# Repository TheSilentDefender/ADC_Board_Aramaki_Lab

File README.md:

# ADC Hub for pGRAMS
- Has 48 ADC channels and an optional voltage divider can be used for RTDs.
- The ADCs only support a range of 0-5V. Any input outside the range may damage the ADCs on board.
- The board outputs ADC integer values with a 12-bit resolution(0-4095)

## How to build
- Install platform.io on Visual Studio Code. You can also install it manually by following the documenation on [the website](https://platformio.org).
- Open the folder using VSC and wait for platform.io to initialize
- Open the platform.io side panel and click build. This should automatically build with the settings in the configuation file.

## How to flash
- Connect to the board in DFU mode or enter in "d" through serial (press the button on the top while you plug in the board)
- Assuming you followed the instuctions for building, you can click on build and upload which will automatic flash the board and restart it.
- If not you can download the bin file and flash it using dfu-util or any other DFU upgrade tool. For example, `sudo dfu-util -a 0 -i 0 -s 0x08000000:leave -D firmware.bin`.

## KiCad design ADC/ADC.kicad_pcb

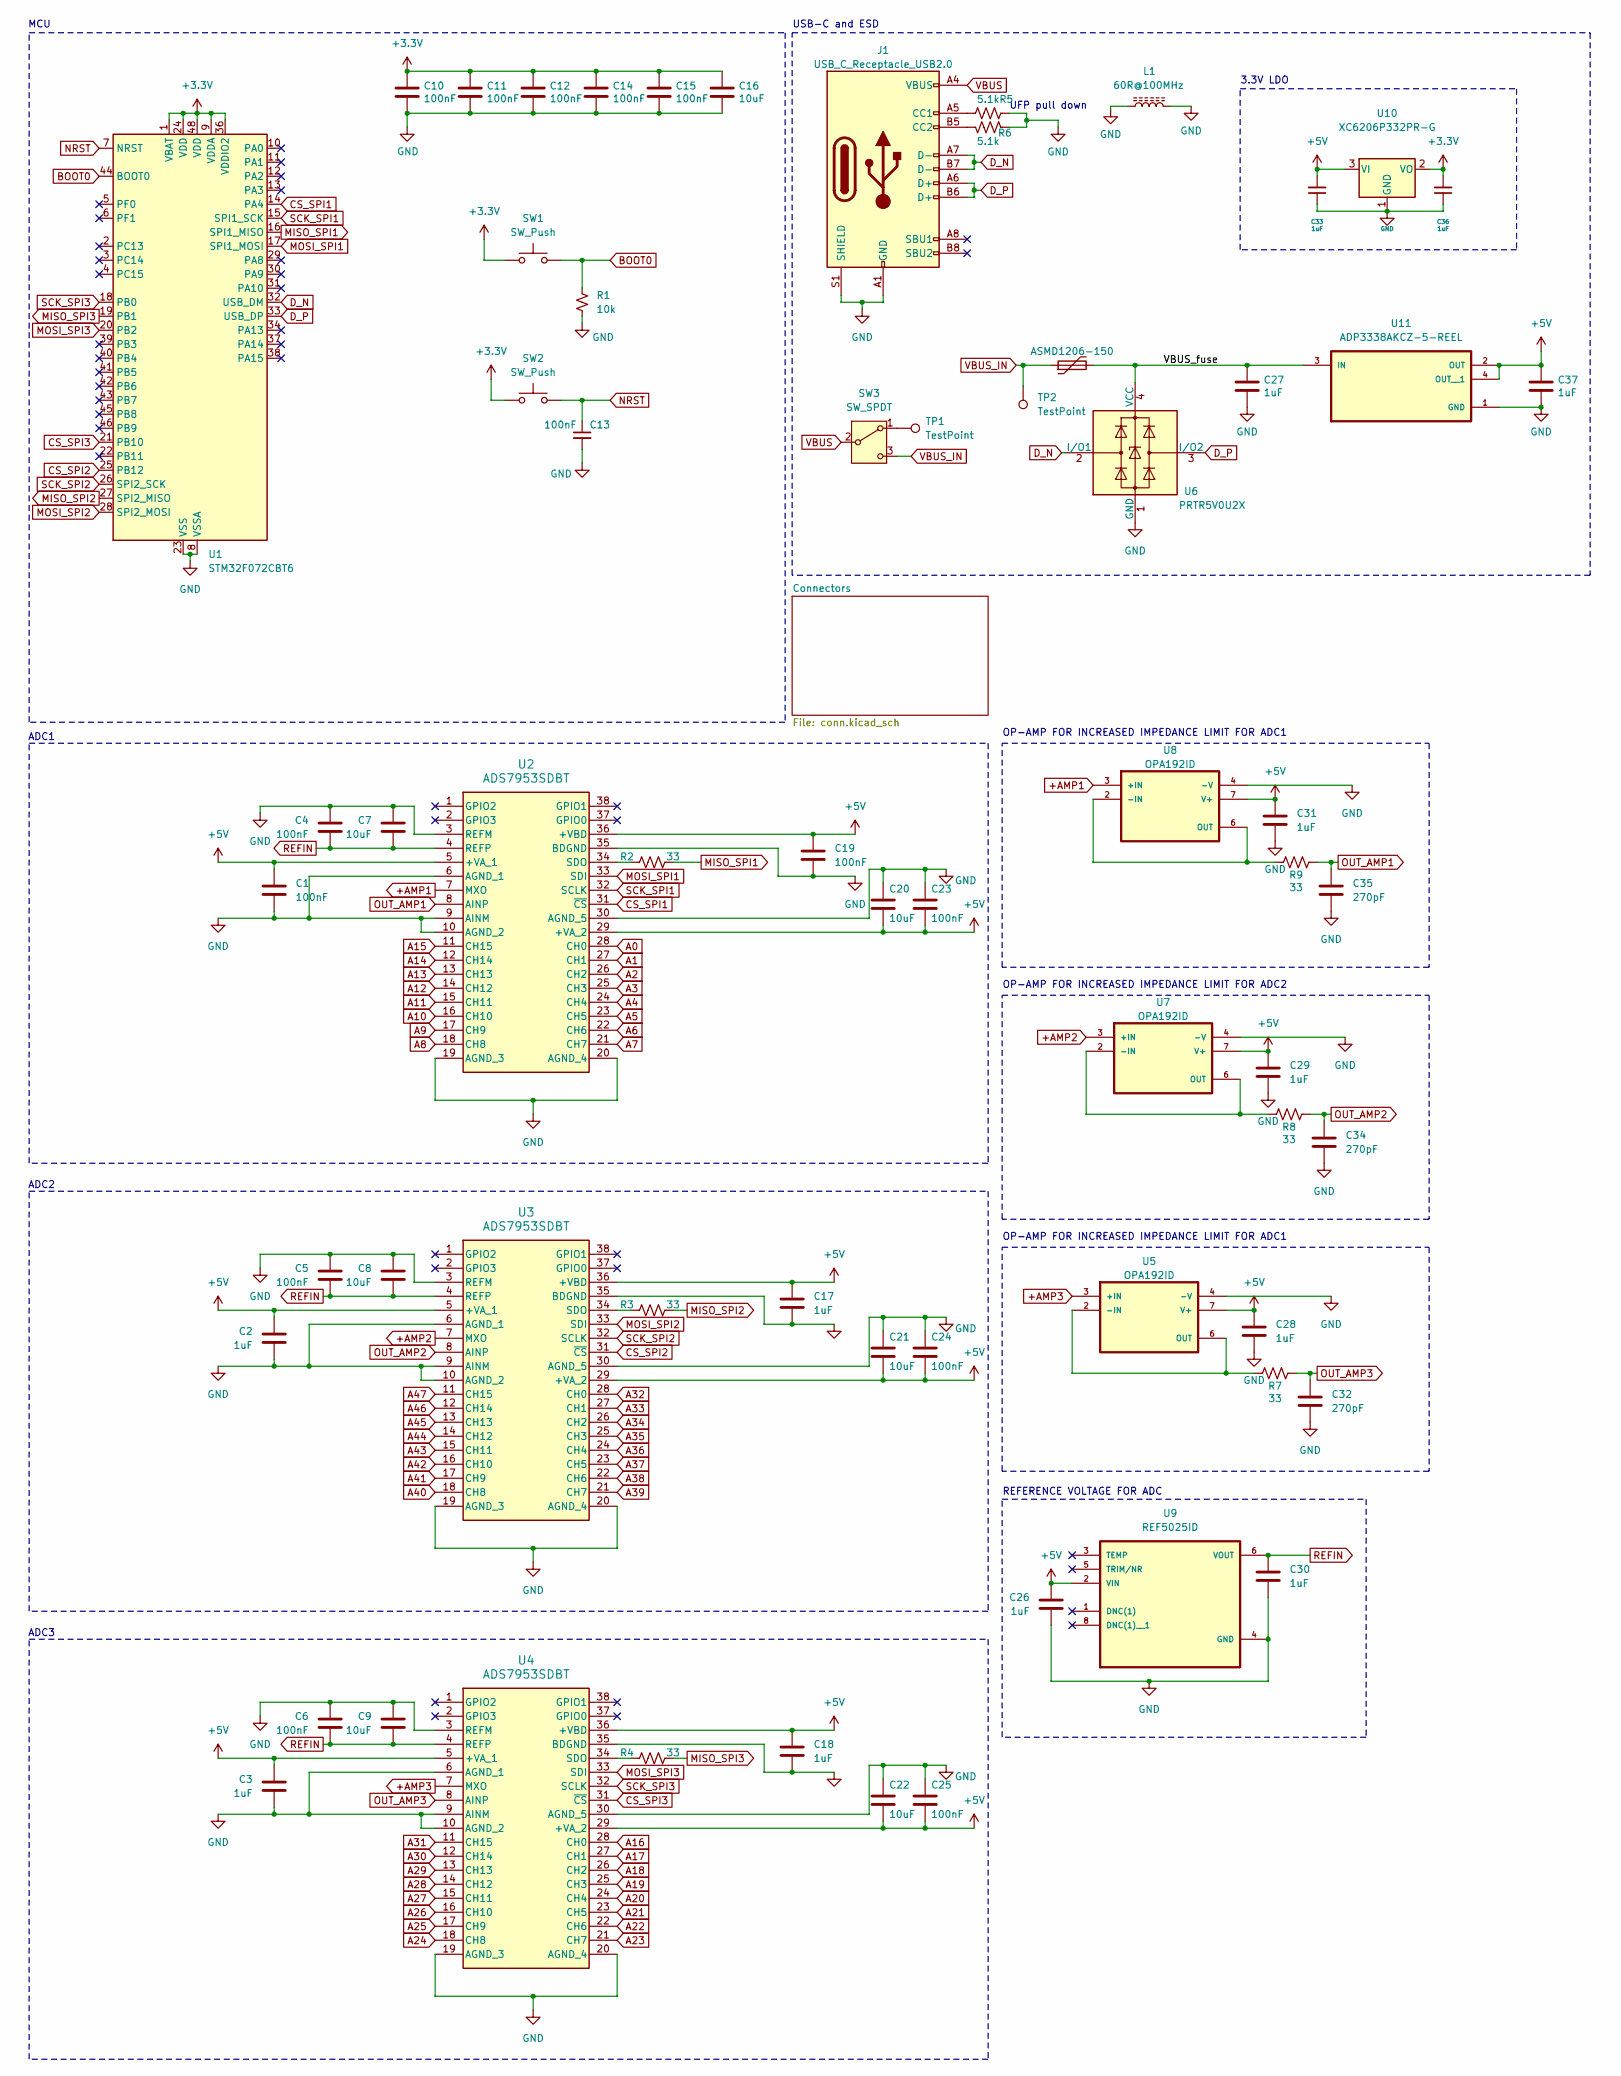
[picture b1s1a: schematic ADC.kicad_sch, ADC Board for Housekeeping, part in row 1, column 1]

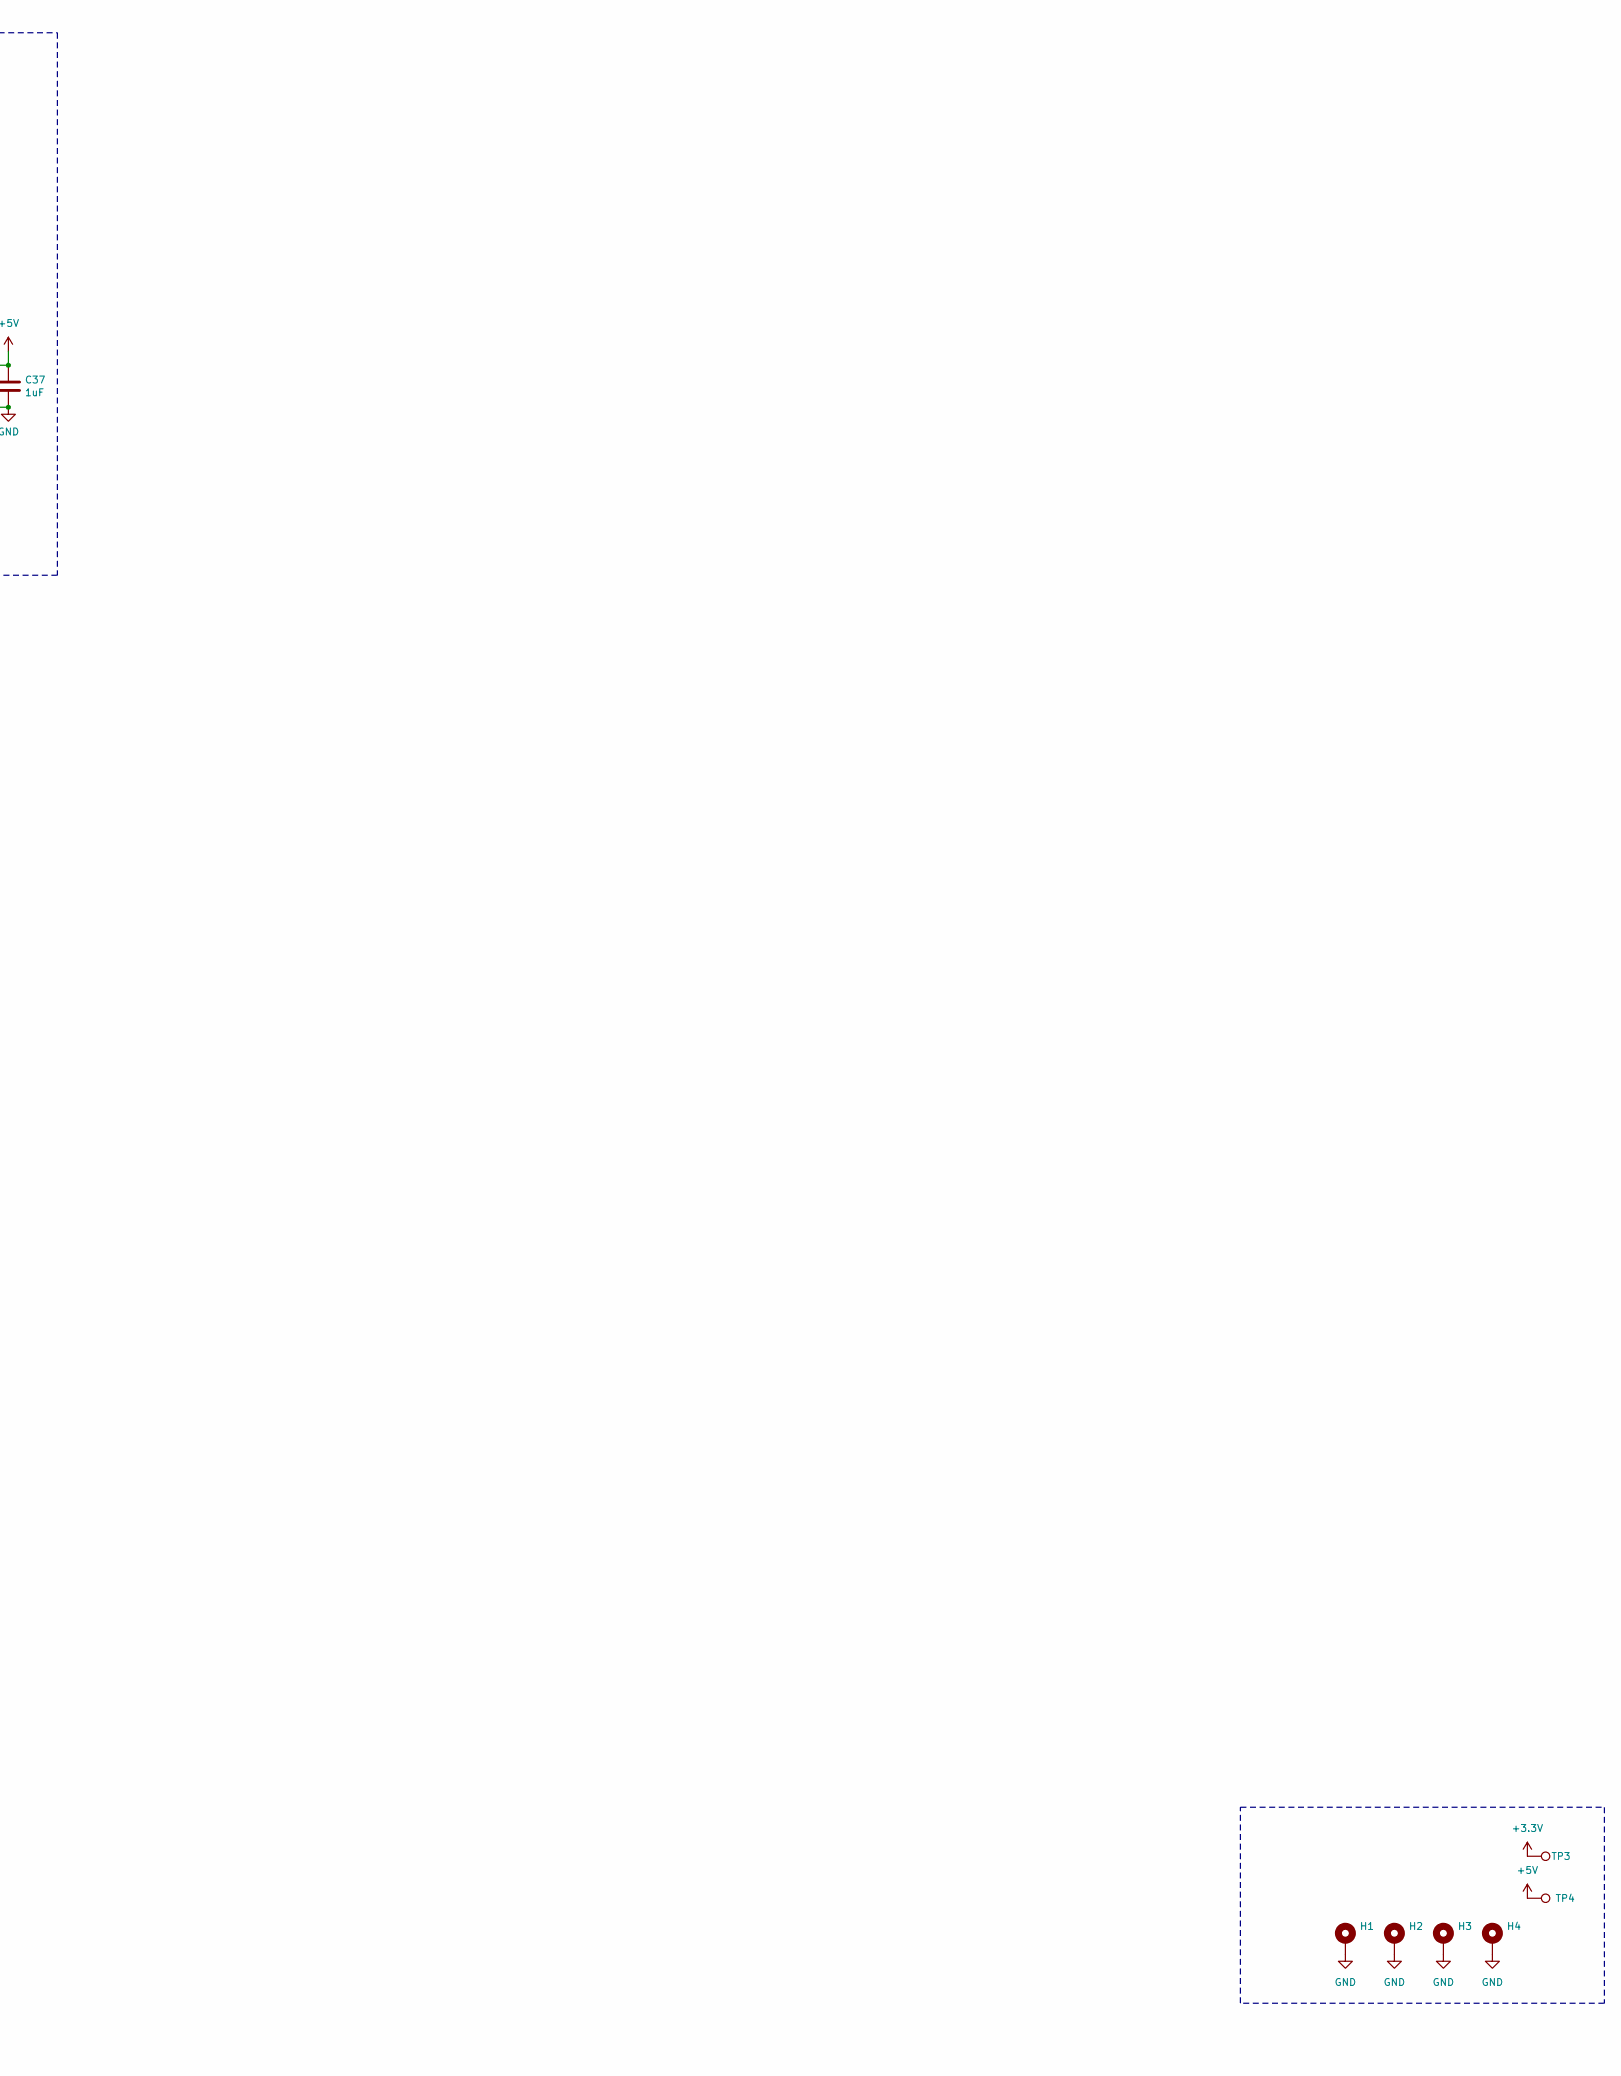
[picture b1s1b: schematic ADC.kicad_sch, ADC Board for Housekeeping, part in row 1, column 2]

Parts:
C1, C4, C5, C6, C19, C23, C24, C25: 100nF; C_0402_1005Metric
C2, C3, C17, C18, C26, C28, C29, C30, C31: 1uF; C_0402_1005Metric
C7, C8, C9, C16, C20, C21, C22: 10uF; C_0402_1005Metric
C10, C11, C12, C13, C14, C15: 100nF; C_0402_1005Metric; LCSC C307331
C27, C37: 1uF; C_0402_1005Metric; LCSC C307331
C32, C34, C35: 270pF; C_0402_1005Metric
C33, C36: 1uF; C_0402_1005Metric; LCSC C52923
F1: ASMD1206-150; Fuse_1206_3216Metric; LCSC C135341
H1, H2, H3, H4: MountingHole_Pad; MountingHole_3mm_Pad
J1: USB_C_Receptacle_USB2.0; USB_C_Receptacle_HRO_TYPE-C-31-M-12; JlcRotOffset 180
L1: 60R@100MHz; L_1206_3216Metric; Manufacturer Part No MLB3216-600P4A(f); LCSC C33600
R1: 10k; R_0402_1005Metric_Pad0.72x0.64mm_HandSolder
R2, R3, R4, R7, R8, R9: 33; R_0402_1005Metric_Pad0.72x0.64mm_HandSolder
R5, R6: 5.1k; R_0402_1005Metric_Pad0.72x0.64mm_HandSolder
SW1, SW2: SW_Push; SW_Push_SPST_NO_Alps_SKRK
SW3: SW_SPDT; SW_SPDT_CK_JS102011SAQN
TP1, TP2, TP3, TP4: TestPoint; TestPoint_Pad_D1.0mm
U1: STM32F072CBT6; LQFP-48_7x7mm_P0.5mm; JlcRotOffset 90
U2, U3, U4: ADS7953SDBT; DBT38
U5, U7, U8: OPA192ID; SOIC127P599X175-8N
U6: PRTR5V0U2X; SOT-143; LCSC C2827688
U9: REF5025ID; SOIC127P599X175-8N
U10: XC6206P332PR-G; SOT-23; LCSC C5446
U11: ADP3338AKCZ-5-REEL; SOT230P700X180-4N

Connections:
+3.3V: C10.1, C11.1, C12.1, C14.1, C15.1, C16.1, C36.2, SW1.1, SW2.1, TP3.1, U1.1 (VBAT), U1.9 (VDDA), U1.24 (VDD), U1.36 (VDDIO2), U1.48 (VDD), U10.2 (VO); also elsewhere on the board
+5V: C1.1, C2.1, C3.1, C17.1, C18.1, C19.1, C20.2, C21.2, C22.2, C23.2, C24.2, C25.2, C26.1, C28.1, C29.1, C31.1, C33.2, C37.1, TP4.1, U2.5 (+VA_1), U2.29 (+VA_2), U2.36 (+VBD), U3.5 (+VA_1), U3.29 (+VA_2), U3.36 (+VBD), U4.5 (+VA_1), U4.29 (+VA_2), U4.36 (+VBD), U5.7 (V+), U7.7 (V+), U8.7 (V+), U9.2 (VIN), U10.3 (VI), U11.2 (OUT), U11.4 (OUT__1); also elsewhere on the board
+AMP1: U2.7 (MXO), U8.3 (+IN)
+AMP2: U3.7 (MXO), U7.3 (+IN)
+AMP3: U4.7 (MXO), U5.3 (+IN)
/VBUS_fuse: C27.1, F1.2, U6.4 (VCC), U11.3 (IN)
A0: U2.28 (CH0); also elsewhere on the board
A1: U2.27 (CH1); also elsewhere on the board
A2: U2.26 (CH2); also elsewhere on the board
A3: U2.25 (CH3); also elsewhere on the board
A4: U2.24 (CH4); also elsewhere on the board
A5: U2.23 (CH5); also elsewhere on the board
A6: U2.22 (CH6); also elsewhere on the board
A7: U2.21 (CH7); also elsewhere on the board
A8: U2.18 (CH8); also elsewhere on the board
A9: U2.17 (CH9); also elsewhere on the board
A10: U2.16 (CH10); also elsewhere on the board
A11: U2.15 (CH11); also elsewhere on the board
A12: U2.14 (CH12); also elsewhere on the board
A13: U2.13 (CH13); also elsewhere on the board
A14: U2.12 (CH14); also elsewhere on the board
A15: U2.11 (CH15); also elsewhere on the board
A16: U4.28 (CH0); also elsewhere on the board
A17: U4.27 (CH1); also elsewhere on the board
A18: U4.26 (CH2); also elsewhere on the board
A19: U4.25 (CH3); also elsewhere on the board
A20: U4.24 (CH4); also elsewhere on the board
A21: U4.23 (CH5); also elsewhere on the board
A22: U4.22 (CH6); also elsewhere on the board
A23: U4.21 (CH7); also elsewhere on the board
A24: U4.18 (CH8); also elsewhere on the board
A25: U4.17 (CH9); also elsewhere on the board
A26: U4.16 (CH10); also elsewhere on the board
A27: U4.15 (CH11); also elsewhere on the board
A28: U4.14 (CH12); also elsewhere on the board
A29: U4.13 (CH13); also elsewhere on the board
A30: U4.12 (CH14); also elsewhere on the board
A31: U4.11 (CH15); also elsewhere on the board
A32: U3.28 (CH0); also elsewhere on the board
A33: U3.27 (CH1); also elsewhere on the board
A34: U3.26 (CH2); also elsewhere on the board
A35: U3.25 (CH3); also elsewhere on the board
A36: U3.24 (CH4); also elsewhere on the board
A37: U3.23 (CH5); also elsewhere on the board
A38: U3.22 (CH6); also elsewhere on the board
A39: U3.21 (CH7); also elsewhere on the board
A40: U3.18 (CH8); also elsewhere on the board
A41: U3.17 (CH9); also elsewhere on the board
A42: U3.16 (CH10); also elsewhere on the board
A43: U3.15 (CH11); also elsewhere on the board
A44: U3.14 (CH12); also elsewhere on the board
A45: U3.13 (CH13); also elsewhere on the board
A46: U3.12 (CH14); also elsewhere on the board
A47: U3.11 (CH15); also elsewhere on the board
BOOT0: R1.1, SW1.2, U1.44 (BOOT0)
CS_SPI1: U1.14 (PA4), U2.31 (~CS)
CS_SPI2: U1.25 (PB12), U3.31 (~CS)
CS_SPI3: U1.21 (PB10), U4.31 (~CS)
D_N: J1.A7 (D-), J1.B7 (D-), U1.32 (USB_DM), U6.2 (I/O1)
D_P: J1.A6 (D+), J1.B6 (D+), U1.33 (USB_DP), U6.3 (I/O2)
GND: C1.2, C2.2, C3.2, C4.1, C5.1, C6.1, C7.1, C8.1, C9.1, C10.2, C11.2, C12.2, C13.2, C14.2, C15.2, C16.2, C17.2, C18.2, C19.2, C20.1, C21.1, C22.1, C23.1, C24.1, C25.1, C26.2, C27.2, C28.2, C29.2, C30.2, C31.2, C32.2, C33.1, C34.2, C35.2, C36.1, C37.2, H1.1, H2.1, H3.1, H4.1, J1.A1 (GND), J1.A12 (GND), J1.B1 (GND), J1.B12 (GND), J1.S1 (SHIELD), L1.1, L1.2, R1.2, R5.1, R6.1, U1.8 (VSSA), U1.23 (VSS), U1.35 (VSS), U1.47 (VSS), U2.3 (REFM), U2.6 (AGND_1), U2.9 (AINM), U2.10 (AGND_2), U2.19 (AGND_3), U2.20 (AGND_4), U2.30 (AGND_5), U2.35 (BDGND), U3.3 (REFM), U3.6 (AGND_1), U3.9 (AINM), U3.10 (AGND_2), U3.19 (AGND_3), U3.20 (AGND_4), U3.30 (AGND_5), U3.35 (BDGND), U4.3 (REFM), U4.6 (AGND_1), U4.9 (AINM), U4.10 (AGND_2), U4.19 (AGND_3), U4.20 (AGND_4), U4.30 (AGND_5), U4.35 (BDGND), U5.4 (-V), U6.1 (GND), U7.4 (-V), U8.4 (-V), U9.4 (GND), U10.1 (GND), U11.1 (GND); also elsewhere on the board
MISO_SPI1: R2.2, U1.16 (SPI1_MISO)
MISO_SPI2: R3.2, U1.27 (SPI2_MISO)
MISO_SPI3: R4.2, U1.19 (PB1)
MOSI_SPI1: U1.17 (SPI1_MOSI), U2.33 (SDI)
MOSI_SPI2: U1.28 (SPI2_MOSI), U3.33 (SDI)
MOSI_SPI3: U1.20 (PB2), U4.33 (SDI)
NRST: C13.1, SW2.2, U1.7 (NRST)
unnamed: J1.A5 (CC1), R5.2
unnamed: J1.B5 (CC2), R6.2
unnamed: SW3.1 (A), TP1.1
unnamed: R2.1, U2.34 (SDO)
unnamed: R3.1, U3.34 (SDO)
unnamed: R4.1, U4.34 (SDO)
unnamed: R7.1, U5.2 (-IN), U5.6 (OUT)
unnamed: R8.1, U7.2 (-IN), U7.6 (OUT)
unnamed: R9.1, U8.2 (-IN), U8.6 (OUT)
OUT_AMP1: C35.1, R9.2, U2.8 (AINP)
OUT_AMP2: C34.1, R8.2, U3.8 (AINP)
OUT_AMP3: C32.1, R7.2, U4.8 (AINP)
REFIN: C4.2, C5.2, C6.2, C7.2, C8.2, C9.2, C30.1, U2.4 (REFP), U3.4 (REFP), U4.4 (REFP), U9.6 (VOUT)
SCK_SPI1: U1.15 (SPI1_SCK), U2.32 (SCLK)
SCK_SPI2: U1.26 (SPI2_SCK), U3.32 (SCLK)
SCK_SPI3: U1.18 (PB0), U4.32 (SCLK)
VBUS: J1.A4 (VBUS), J1.A9 (VBUS), J1.B4 (VBUS), J1.B9 (VBUS), SW3.2 (B)
VBUS_IN: F1.1, SW3.3 (C), TP2.1

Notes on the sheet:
OP-AMP FOR INCREASED IMPEDANCE LIMIT FOR ADC1
MCU
OP-AMP FOR INCREASED IMPEDANCE LIMIT FOR ADC2
UFP pull down
ADC1
REFERENCE VOLTAGE FOR ADC
ADC3
3.3V LDO
USB-C and ESD
ADC2

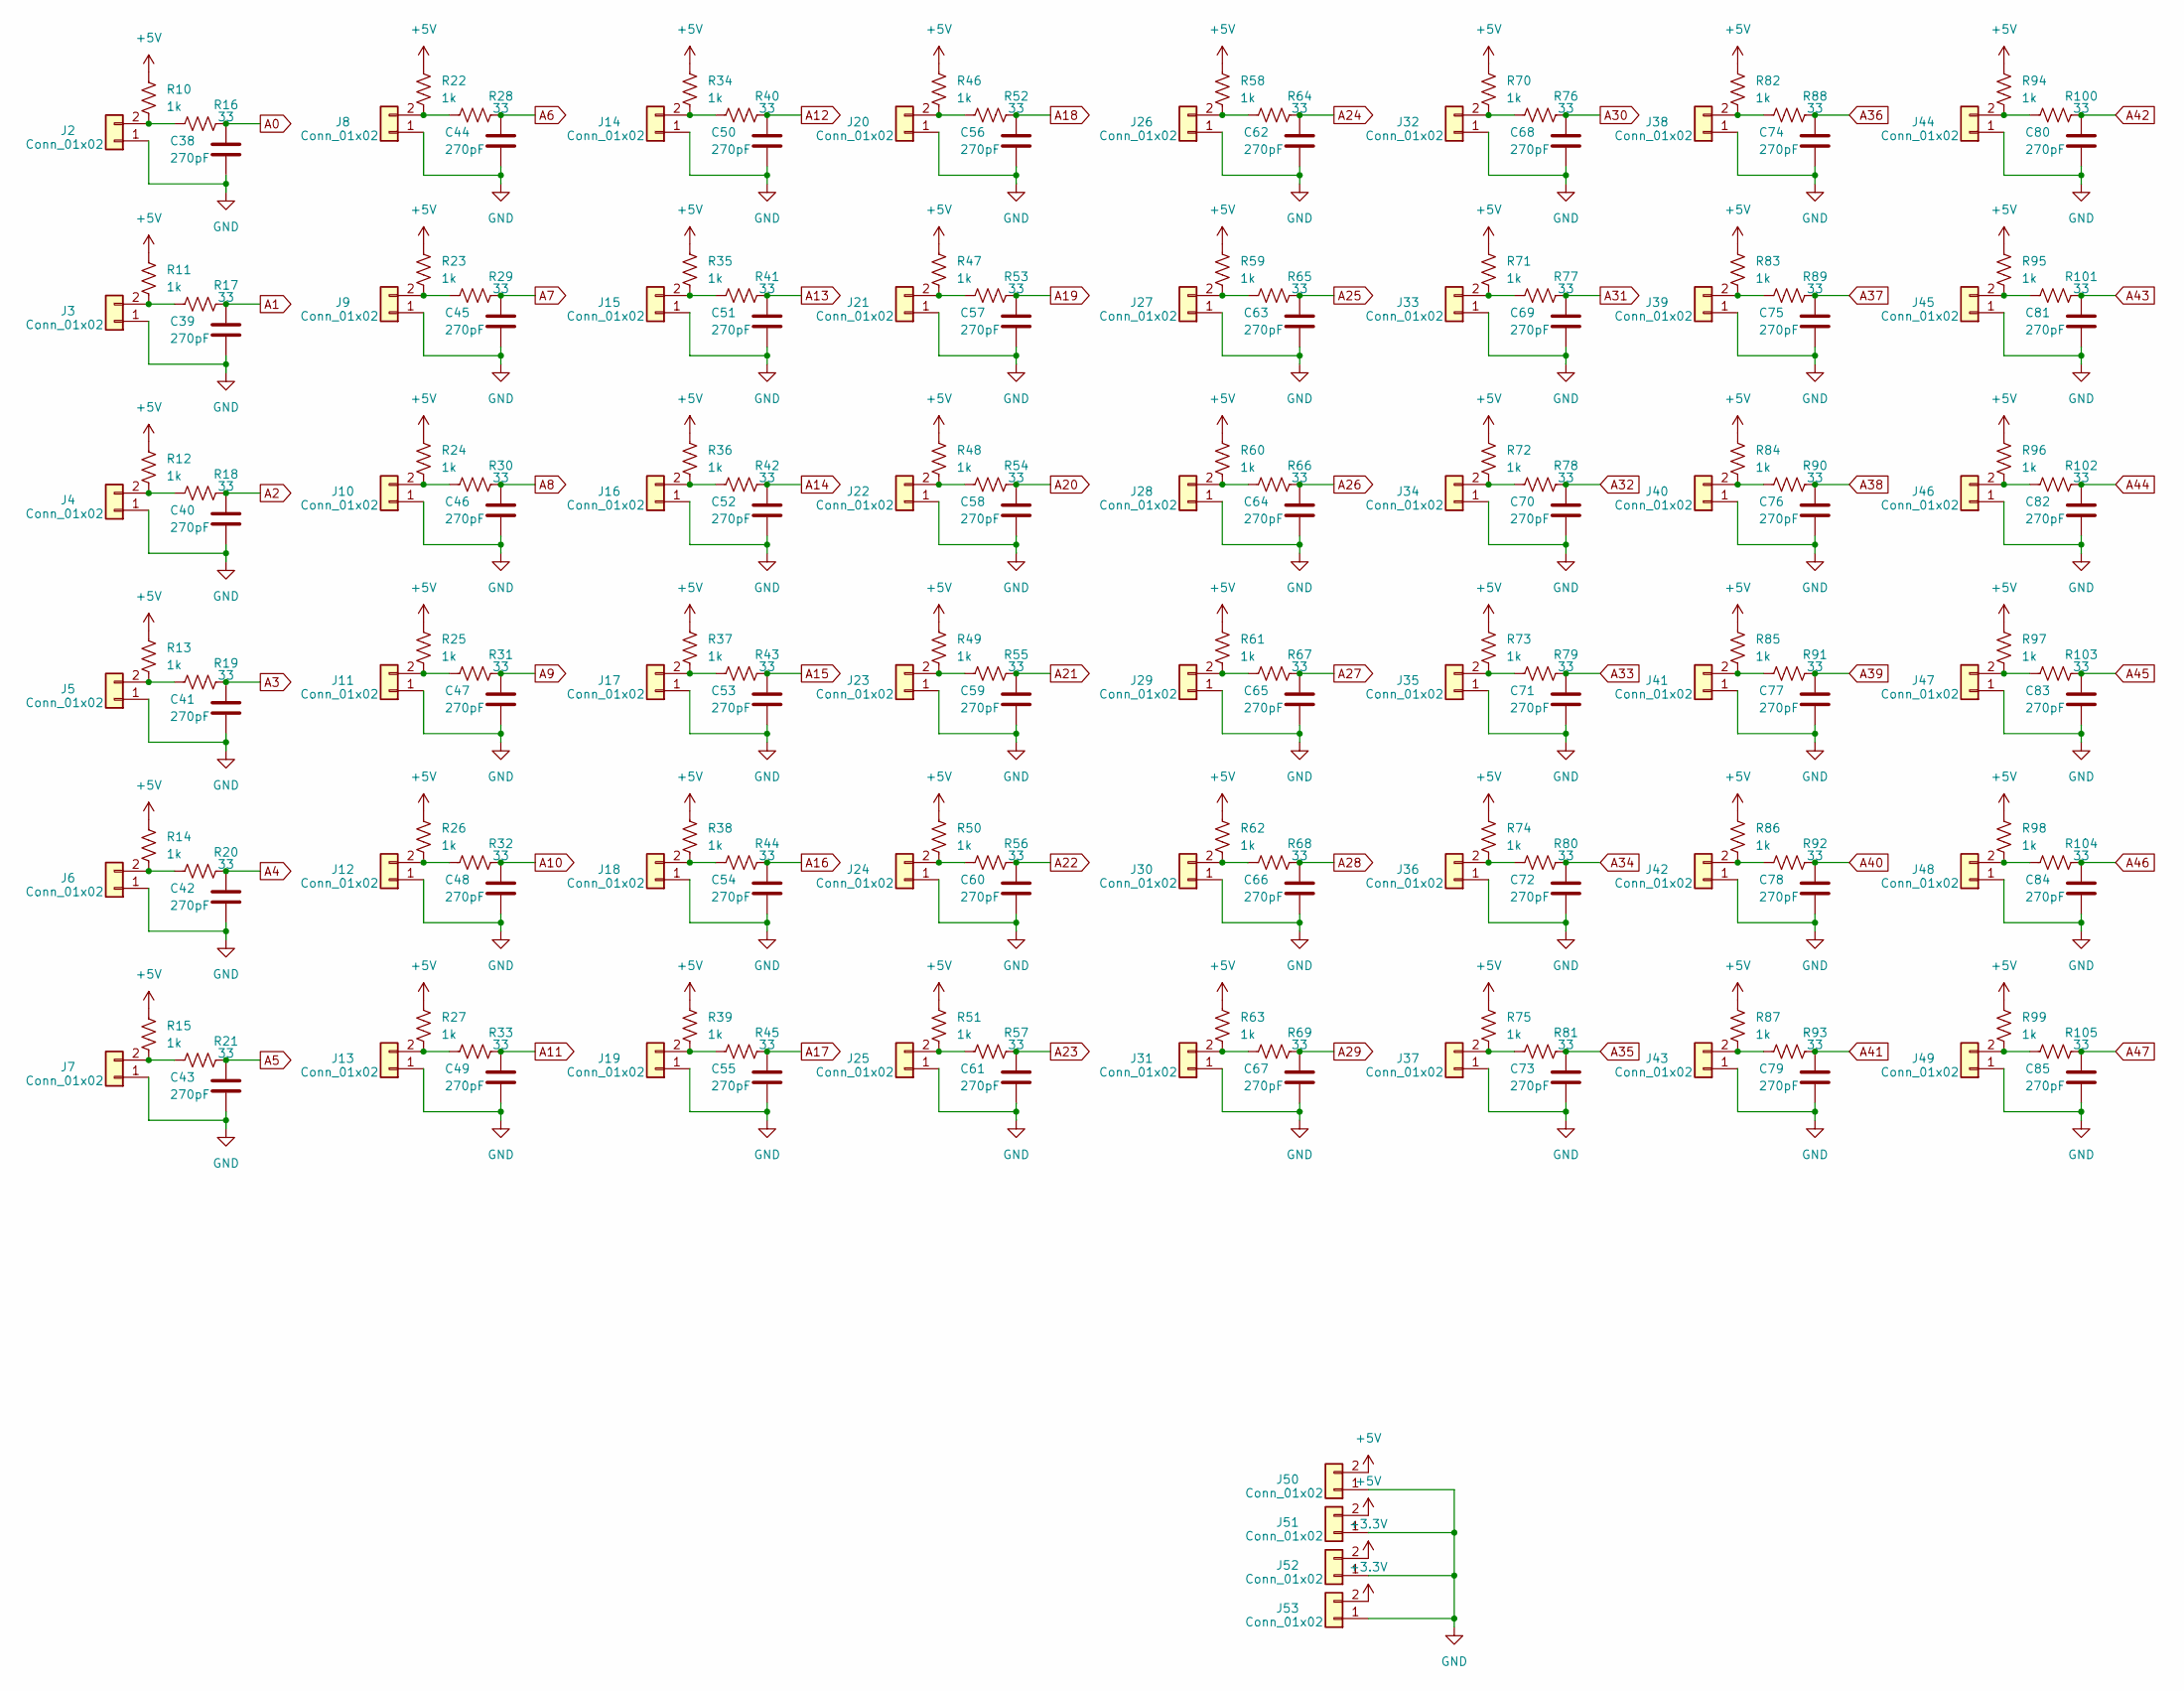
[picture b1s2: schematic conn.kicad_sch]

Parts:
C38, C39, C40, C41, C42, C43, C44, C45, C46, C47, C48, C49, C50, C51, C52, C53, C54, C55, C56, C57, C58, C59, C60, C61, C62, C63, C64, C65, C66, C67, C68, C69, C70, C71, C72, C73, C74, C75, C76, C77, C78, C79, C80, C81, C82, C83, C84, C85: 270pF; C_0402_1005Metric
J2, J3, J4, J5, J6, J7, J8, J9, J10, J11, J12, J13, J14, J15, J16, J17, J18, J19, J20, J21, J22, J23, J24, J25, J26, J27, J28, J29, J30, J31, J32, J33, J34, J35, J36, J37, J38, J39, J40, J41, J42, J43, J44, J45, J46, J47, J48, J49: Conn_01x02; Molex_Mini-Fit_Jr_5566-02A_2x01_P4.20mm_Vertical
J50, J51, J52, J53: Conn_01x02; PinHeader_1x02_P2.54mm_Vertical
R10, R11, R12, R13, R14, R15, R22, R23, R24, R25, R26, R27, R34, R35, R36, R37, R38, R39, R46, R47, R48, R49, R50, R51, R58, R59, R60, R61, R62, R63, R70, R71, R72, R73, R74, R75, R82, R83, R84, R85, R86, R87, R94, R95, R96, R97, R98, R99: 1k; R_0603_1608Metric_Pad0.98x0.95mm_HandSolder
R16, R17, R18, R19, R20, R21, R28, R29, R30, R31, R32, R33, R40, R41, R42, R43, R44, R45, R52, R53, R54, R55, R56, R57, R64, R65, R66, R67, R68, R69, R76, R77, R78, R79, R80, R81, R88, R89, R90, R91, R92, R93, R100, R101, R102, R103, R104, R105: 33; R_0402_1005Metric_Pad0.72x0.64mm_HandSolder

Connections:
+3.3V: J52.2, J53.2; also elsewhere on the board
+5V: J50.2, J51.2, R10.1, R11.1, R12.1, R13.1, R14.1, R15.1, R22.1, R23.1, R24.1, R25.1, R26.1, R27.1, R34.1, R35.1, R36.1, R37.1, R38.1, R39.1, R46.1, R47.1, R48.1, R49.1, R50.1, R51.1, R58.1, R59.1, R60.1, R61.1, R62.1, R63.1, R70.1, R71.1, R72.1, R73.1, R74.1, R75.1, R82.1, R83.1, R84.1, R85.1, R86.1, R87.1, R94.1, R95.1, R96.1, R97.1, R98.1, R99.1; also elsewhere on the board
A0: C38.1, R16.2; also elsewhere on the board
A1: C39.1, R17.2; also elsewhere on the board
A2: C40.1, R18.2; also elsewhere on the board
A3: C41.1, R19.2; also elsewhere on the board
A4: C42.1, R20.2; also elsewhere on the board
A5: C43.1, R21.2; also elsewhere on the board
A6: C44.1, R28.2; also elsewhere on the board
A7: C45.1, R29.2; also elsewhere on the board
A8: C46.1, R30.2; also elsewhere on the board
A9: C47.1, R31.2; also elsewhere on the board
A10: C48.1, R32.2; also elsewhere on the board
A11: C49.1, R33.2; also elsewhere on the board
A12: C50.1, R40.2; also elsewhere on the board
A13: C51.1, R41.2; also elsewhere on the board
A14: C52.1, R42.2; also elsewhere on the board
A15: C53.1, R43.2; also elsewhere on the board
A16: C54.1, R44.2; also elsewhere on the board
A17: C55.1, R45.2; also elsewhere on the board
A18: C56.1, R52.2; also elsewhere on the board
A19: C57.1, R53.2; also elsewhere on the board
A20: C58.1, R54.2; also elsewhere on the board
A21: C59.1, R55.2; also elsewhere on the board
A22: C60.1, R56.2; also elsewhere on the board
A23: C61.1, R57.2; also elsewhere on the board
A24: C62.1, R64.2; also elsewhere on the board
A25: C63.1, R65.2; also elsewhere on the board
A26: C64.1, R66.2; also elsewhere on the board
A27: C65.1, R67.2; also elsewhere on the board
A28: C66.1, R68.2; also elsewhere on the board
A29: C67.1, R69.2; also elsewhere on the board
A30: C68.1, R76.2; also elsewhere on the board
A31: C69.1, R77.2; also elsewhere on the board
A32: C70.1, R78.2; also elsewhere on the board
A33: C71.1, R79.2; also elsewhere on the board
A34: C72.1, R80.2; also elsewhere on the board
A35: C73.1, R81.2; also elsewhere on the board
A36: C74.1, R88.2; also elsewhere on the board
A37: C75.1, R89.2; also elsewhere on the board
A38: C76.1, R90.2; also elsewhere on the board
A39: C77.1, R91.2; also elsewhere on the board
A40: C78.1, R92.2; also elsewhere on the board
A41: C79.1, R93.2; also elsewhere on the board
A42: C80.1, R100.2; also elsewhere on the board
A43: C81.1, R101.2; also elsewhere on the board
A44: C82.1, R102.2; also elsewhere on the board
A45: C83.1, R103.2; also elsewhere on the board
A46: C84.1, R104.2; also elsewhere on the board
A47: C85.1, R105.2; also elsewhere on the board
GND: C38.2, C39.2, C40.2, C41.2, C42.2, C43.2, C44.2, C45.2, C46.2, C47.2, C48.2, C49.2, C50.2, C51.2, C52.2, C53.2, C54.2, C55.2, C56.2, C57.2, C58.2, C59.2, C60.2, C61.2, C62.2, C63.2, C64.2, C65.2, C66.2, C67.2, C68.2, C69.2, C70.2, C71.2, C72.2, C73.2, C74.2, C75.2, C76.2, C77.2, C78.2, C79.2, C80.2, C81.2, C82.2, C83.2, C84.2, C85.2, J2.1, J3.1, J4.1, J5.1, J6.1, J7.1, J8.1, J9.1, J10.1, J11.1, J12.1, J13.1, J14.1, J15.1, J16.1, J17.1, J18.1, J19.1, J20.1, J21.1, J22.1, J23.1, J24.1, J25.1, J26.1, J27.1, J28.1, J29.1, J30.1, J31.1, J32.1, J33.1, J34.1, J35.1, J36.1, J37.1, J38.1, J39.1, J40.1, J41.1, J42.1, J43.1, J44.1, J45.1, J46.1, J47.1, J48.1, J49.1, J50.1, J51.1, J52.1, J53.1; also elsewhere on the board
unnamed: J2.2, R10.2, R16.1
unnamed: J3.2, R11.2, R17.1
unnamed: J4.2, R12.2, R18.1
unnamed: J5.2, R13.2, R19.1
unnamed: J6.2, R14.2, R20.1
unnamed: J7.2, R15.2, R21.1
unnamed: J8.2, R22.2, R28.1
unnamed: J9.2, R23.2, R29.1
unnamed: J10.2, R24.2, R30.1
unnamed: J11.2, R25.2, R31.1
unnamed: J12.2, R26.2, R32.1
unnamed: J13.2, R27.2, R33.1
unnamed: J14.2, R34.2, R40.1
unnamed: J15.2, R35.2, R41.1
unnamed: J16.2, R36.2, R42.1
unnamed: J17.2, R37.2, R43.1
unnamed: J18.2, R38.2, R44.1
unnamed: J19.2, R39.2, R45.1
unnamed: J20.2, R46.2, R52.1
unnamed: J21.2, R47.2, R53.1
unnamed: J22.2, R48.2, R54.1
unnamed: J23.2, R49.2, R55.1
unnamed: J24.2, R50.2, R56.1
unnamed: J25.2, R51.2, R57.1
unnamed: J26.2, R58.2, R64.1
unnamed: J27.2, R59.2, R65.1
unnamed: J28.2, R60.2, R66.1
unnamed: J29.2, R61.2, R67.1
unnamed: J30.2, R62.2, R68.1
unnamed: J31.2, R63.2, R69.1
unnamed: J32.2, R70.2, R76.1
unnamed: J33.2, R71.2, R77.1
unnamed: J34.2, R72.2, R78.1
unnamed: J35.2, R73.2, R79.1
unnamed: J36.2, R74.2, R80.1
unnamed: J37.2, R75.2, R81.1
unnamed: J38.2, R82.2, R88.1
unnamed: J39.2, R83.2, R89.1
unnamed: J40.2, R84.2, R90.1
unnamed: J41.2, R85.2, R91.1
unnamed: J42.2, R86.2, R92.1
unnamed: J43.2, R87.2, R93.1
unnamed: J44.2, R94.2, R100.1
unnamed: J45.2, R95.2, R101.1
unnamed: J46.2, R96.2, R102.1
unnamed: J47.2, R97.2, R103.1
unnamed: J48.2, R98.2, R104.1
unnamed: J49.2, R99.2, R105.1

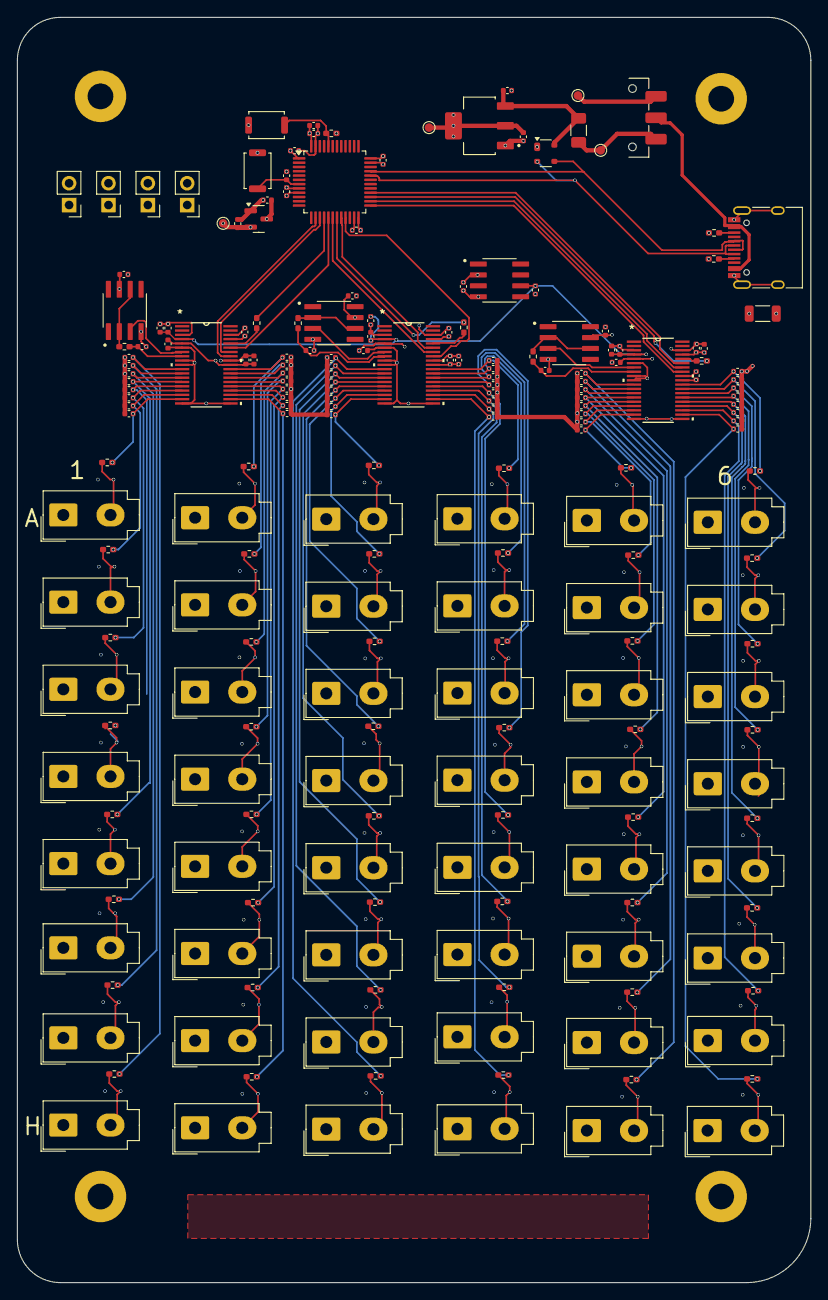
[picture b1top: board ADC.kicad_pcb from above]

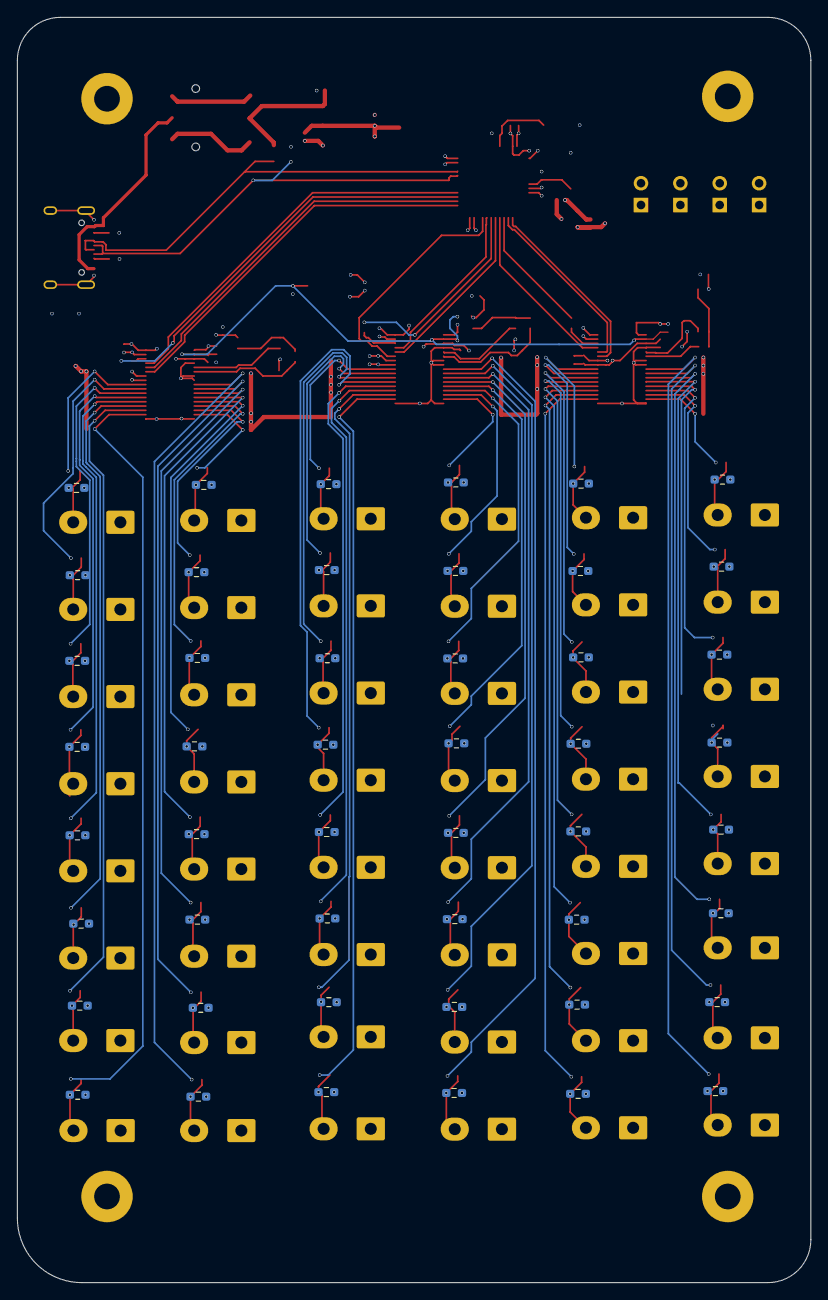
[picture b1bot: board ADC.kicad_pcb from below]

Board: 4 copper layers, 92.5 x 147.5 mm, 267 parts (48 on the bottom side), 134 nets.

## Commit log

2024-06-27 Create LICENCE
2024-06-28 uploaded based code and pcb
2024-06-28 updated gitignore
2024-07-04 added SPI code
2024-07-08 removed files
2024-07-15 reading all channels working
2024-07-15 doubled range
2024-07-25 updated schematic to match the eval kit
2024-07-26 finished V2
2024-07-29 updated v2
2024-07-29 updated gerbers
2024-07-30 updated sch pdf
2024-09-17 updated code
2024-09-18 32 channels working
2024-09-19 binary output
2024-10-04 float print
2024-11-15 pcb update
2025-05-16 added remote dfu and reset
2025-11-04 Start readout script
2026-01-07 Fix channel indexing error in firmware
2026-01-20 Update readout script; add config reading and live RTD plotting
